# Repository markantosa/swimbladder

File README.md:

# SwimBladder

Power distribution board (PDB) project files for the SwimBladder project.

Silkscreen tag: `SOAR UWU | 8 x T200 | V1.1`

> [!WARNING]
> This board is an unvalidated, untested work in progress (WIP).
> It has not completed electrical, thermal, or in-water system validation.
> Do not treat this design as production-ready hardware.

## Project Status

- Current state: WIP (design in progress)
- Revision: V1.1
- Validation status: not electrically validated
- Test status: not thermally validated, not full-load validated, not field-tested
- Use at your own risk until formal verification is completed

## Repository Contents

- `KiCad Project Files v1.1/` - **Canonical** KiCad project, PCB, schematic, and the
  `SwimBladder Custom Footprints` library. Open `KiCad Project Files v1.1/UWU PDB.kicad_pro`.
- `KiCad Project Files/` - Deprecated earlier project set, kept for history. Do not edit.
- `SwimBladder PDB.kicad_sch` (repo root) - Stale May snapshot, superseded by the schematic
  inside `KiCad Project Files v1.1/`. Do not use.
- `Screenshots/` - Board and schematic screenshots. `v1.1 *.png` are current; the unprefixed
  files are the earlier V1.0 captures.
- `SwimBladderV1.0.step` - 3D board model (V1.0 geometry).
- `Swim_Bladder_Doc_v3_0.pdf` - Full engineering reference and calculations. Component values
  in this PDF predate the V1.1 schematic changes listed below.

## Project Overview

This board is designed as a compact 8-thruster central star-node PDB for Blue Robotics T200
systems with 4S battery input. It is currently in a pre-validation state and should be treated
as a reference design draft.

- System topology: battery -> cable-side main fuse -> optional e-stop/contactor -> dual XT90 input -> central high-current node -> 8 fused ESC branches -> XT60 outputs
- Nominal battery voltage: 14.8 V (4S), full charge: 16.8 V
- Thruster design current: about 25 A each
- Total design current: 200 A (with burst targets up to around 280-300 A)
- Per-branch fuse target: 30 A

## Schematic Summary (V1.1)

### Input / central node
- Dual XT90 input connectors (`J1`, `J19`) feeding one common +VBAT star node, symmetrical wiring for current sharing.
- Bulk capacitance at the node: `C_MAIN1`, `C_MAIN2` = 4700 uF each.
- Input TVS: `D1` (`D_TVS`), 22-24 V standoff class for 4S. Recommended part: SMDJ22A
  (unidirectional, 3 kW, DO-214AB / SMC footprint, `Diode_SMD:D_SMC` or `D_SMC_HandSolder`).
- Rail bleed / discharge: `R_BLEED1` = 22 kOhm. Draws ~0.76 mA / ~13 mW continuously at full
  charge - trivial dissipation for a 0603, well within its power/voltage rating.
- Power/status LED: `D2` (`LED`) with series resistor `R_LED1` = 10 kOhm.

### Per-ESC branch (x8)
- Branch fuse: `F_ESC1..F_ESC8` = 30 A.
- Branch bulk cap: `C_ESC1..C_ESC8` = 1000 uF.
- Branch high-frequency cap: `C_HF1..C_HF8` = 1 uF.
- Output: `J3..J10`, XT60 per branch.
- Branch decoupling is now two caps (1000 uF + 1 uF). The earlier third per-branch cap
  (1 nF high-frequency) has been removed - on a high-current motor branch it contributes
  negligible benefit and can create anti-resonance with the larger caps.

### PWM signal
- 16-pin IDC header `J2` (`Conn_02x08_Odd_Even`, 2x8, 2.54 mm), alternating PWM / GND pins.
  Suggested part footprint: `Connector_IDC:IDC-Header_2x08_P2.54mm_Vertical`.
- Individual PWM channel inputs: `J11..J18` (PWM1..PWM8).
- Per-channel series resistor: `R_PWM1..R_PWM8` = 100 Ohm.
- Per-channel pulldown resistor: `R_PD1..R_PD8` = 10 kOhm.

## Passive Footprint Notes

- PWM channel series resistors (`R_PWM*`): 0402 hand-solder land pattern
  (`Resistor_SMD:R_0402_1005Metric_Pad0.72x0.64mm_HandSolder`) for IDC header pitch.
- All other signal passives (`R_BLEED1`, `R_LED1`, `R_PD*`) and branch HF caps: 0603
  hand-solder (`R_0603_1608Metric_Pad0.98x0.95mm_HandSolder` /
  `C_0603_1608Metric_Pad1.08x0.95mm_HandSolder`).
- Custom / project-specific footprints live in `KiCad Project Files v1.1/SwimBladder Custom Footprints`.

## Key Engineering Notes (from the PDF)

- Architecture: single compact central +VBAT node, not dual banks, for a roughly 90 mm x 90 mm board.
- Safety: main fuse should be upstream on the battery cable (recommended 225-250 A), close to the battery.
- Copper strategy: use a short, wide, via-stitched central polygon (L1 + L3 for +VBAT), and strong common ground return (L2 + L4).
- Copper thickness for the 200 A / 300 A rating: 1 oz (35 um) is not sufficient. Spec 2 oz
  (70 um) minimum on the outer layers, 3 oz preferred, and carry +VBAT and GND on two layers
  each in parallel (~4 oz-equivalent per net) with dense inter-layer via stitching. Treat the
  central node as a plane, not a trace, and size pours/vias for <= 20-30 C rise. Per-branch
  (~25 A): 2 oz outer with ~10-15 mm pour width is adequate.
- Via stitching: use two via classes - large power vias (~1.2 mm pad / 0.6 mm drill or bigger)
  for the +VBAT node and ground return, and a smaller class (~0.6-0.8 mm pad / 0.3-0.4 mm drill)
  for signal-ground / thermal stitching around the PWM header.
- Branch geometry: practical branch widths around 12-15 mm (8-10 mm absolute compact minimum for very short sections).
- Connectors: dual XT90 input for current sharing (symmetrical wiring), XT60 per ESC branch preferred.
- Protection/passives: 22-24 V standoff TVS class for 4S input, bulk capacitance near input/node plus branch-level capacitors.
- Signal: 16-pin IDC PWM header with alternating PWM/GND and per-channel series + pulldown resistors.

## Known Issues / TODO (V1.1)

- No outstanding items. TVS placement, input HF cap grouping, indicator LEDs, and the
  `R_BLEED1` value (now 22 kOhm) have all been resolved.

## Quick Calculation Snapshot

- Per thruster power at 16 V and 25 A: 400 W
- System power for 8 thrusters: 3200 W
- Example central copper section in the doc (50 mm width, 140 um thickness, 25 mm length, one layer):
	- Estimated R ~= 0.0616 mOhm
	- Vdrop at 200 A ~= 0.012 V
	- Copper loss at 200 A ~= 2.46 W

For complete assumptions, formulas, BOM guidance, and test plan, see `Swim_Bladder_Doc_v3_0.pdf`.

## Screenshots (V1.1)

| Assembled Board (1) | Assembled Board (2) |
|---|---|
|  |  |

| Routing | 3D Render - Top | 3D Render - Isometric |
|---|---|---|
|  |  |  |

<sub>Earlier V1.0 captures (`Schematic.png`, `PCB Editor View.png`, `3D View.png`) remain in `Screenshots/` for reference.</sub>

## Getting Started

1. Install KiCad (recommended version 8+).
2. Open the project from `KiCad Project Files v1.1/UWU PDB.kicad_pro`.
3. Review schematic, layout, and engineering assumptions from the PDF before fabrication,
   noting the V1.1 changes and open TODO items above.

## Changelog

### V1.1 (in progress)
- Canonical project files moved to `KiCad Project Files v1.1/`; earlier `KiCad Project Files/`
  and the repo-root `SwimBladder PDB.kicad_sch` are deprecated.
- Added `SwimBladder Custom Footprints` library.
- Main bulk capacitance specified as `C_MAIN1/2` = 4700 uF each.
- Removed the 1 nF per-branch decoupling cap; branches now use 1000 uF + 1 uF only.
- PWM front-end defined: `R_PWM*` = 100 Ohm series, `R_PD*` = 10 kOhm pulldown, inputs `J11..J18`.
- Added rail bleed resistor `R_BLEED1` (value still a placeholder) and status LED `D2` / `R_LED1`.
- Input TVS `D1` present; placement correction pending (see Known Issues).

### V1.0
- Initial 8-branch central star-node PDB layout.

## Procurement (2-board build)

Bare PCB via JLCPCB; most components via LCSC (`SwimBladder_LCSC_BatchBOM_v1.1.csv`); full
reference BOM in `SwimBladder_BOM_v1.1.csv`. JLCPCB and LCSC ship separately even though they're
sister companies - no combined-box option outside of paying for JLC's PCBA assembly service.

### Still need to source separately (not in the LCSC batch order)
- [ ] `R_BLEED1`, 22k Ohm, 0603 (LCSC C114065) - MOQ is Min:100/Mult:100, not worth it for ~3
  pieces; ask around for spares or buy loose.
- [ ] `R_LED1` + `R_PD1..R_PD8`, 10k Ohm, 0603 (LCSC C98220) - same MOQ issue, ~23 pieces needed.
- [ ] 30 A mini blade fuse elements (x16) for `F_ESC1..F_ESC8` - these plug into the Keystone 3568
  holder (which is in the LCSC order) but the fuse element itself isn't an LCSC/electronics-
  distributor item; source from an automotive parts store or RC supplier.
- [ ] `F_ESC1..F_ESC8` fuseholders, Keystone 3568 (x8) - LCSC C5249699 was out of stock, dropped
  from the batch order; source from Digi-Key/Mouser instead.

### Already owned, not in the order
- `D2` status LED
- `J2` IDC 2x08 header
- `R_PWM1..R_PWM8`, 100 Ohm, 0402 (from sample book)

## License

This project is licensed under the MIT License. See the LICENSE file for details.

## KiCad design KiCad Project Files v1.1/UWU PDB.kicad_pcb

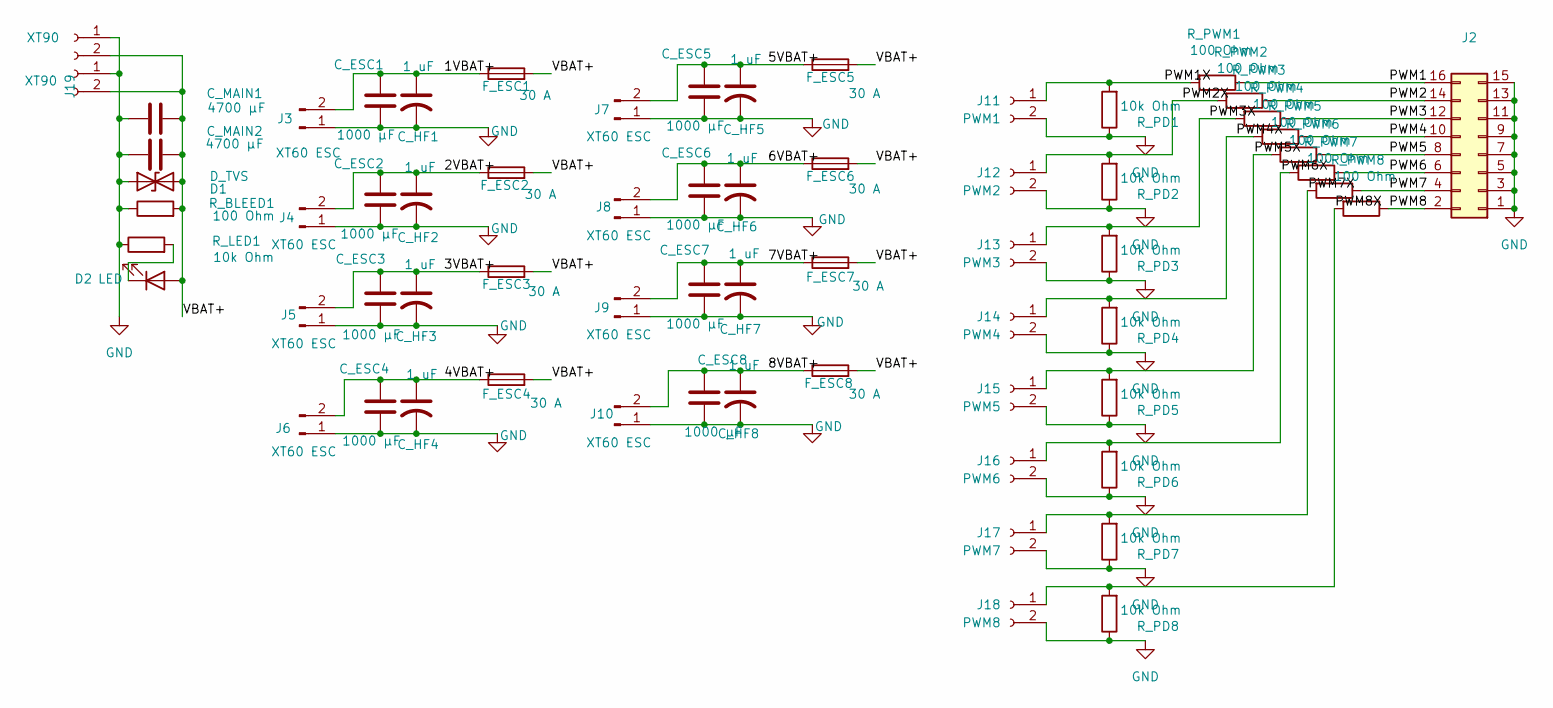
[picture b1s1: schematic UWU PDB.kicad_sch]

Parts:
C_ESC1, C_ESC2, C_ESC3, C_ESC4, C_ESC5, C_ESC6, C_ESC7, C_ESC8: 1000 µF; CP_Radial_D12.5mm_P5.00mm
C_HF1, C_HF2, C_HF3, C_HF4, C_HF5, C_HF6, C_HF7, C_HF8: 1 uF; C_0603_1608Metric_Pad1.08x0.95mm_HandSolder
C_MAIN1, C_MAIN2: 4700 µF; CP_Radial_D16.0mm_P7.50mm
D1: D_TVS; D_SMC
D2: LED; LED_1206_3216Metric
F_ESC1, F_ESC2, F_ESC3, F_ESC4, F_ESC5, F_ESC6, F_ESC7, F_ESC8: 30 A; Fuseholder_Blade_Mini_Keystone_3568
J1, J19: XT90; AMASS_XT90PW-M_1x02_P10.90mm_Horizontal
J2: Conn_02x08_Odd_Even; IDC-Header_2x08_P2.54mm_Vertical
J3, J4, J5, J6, J7, J8, J9, J10: XT60 ESC; AMASS_XT60PW-F_1x02_P7.20mm_Horizontal
J11: PWM1; Molex_Micro-Fit_3.0_43650-0200_1x02_P3.00mm_Horizontal
J12: PWM2; Molex_Micro-Fit_3.0_43650-0200_1x02_P3.00mm_Horizontal
J13: PWM3; Molex_Micro-Fit_3.0_43650-0200_1x02_P3.00mm_Horizontal
J14: PWM4; Molex_Micro-Fit_3.0_43650-0200_1x02_P3.00mm_Horizontal
J15: PWM5; Molex_Micro-Fit_3.0_43650-0200_1x02_P3.00mm_Horizontal
J16: PWM6; Molex_Micro-Fit_3.0_43650-0200_1x02_P3.00mm_Horizontal
J17: PWM7; Molex_Micro-Fit_3.0_43650-0200_1x02_P3.00mm_Horizontal
J18: PWM8; Molex_Micro-Fit_3.0_43650-0200_1x02_P3.00mm_Horizontal
R_BLEED1: 100 Ohm; R_0603_1608Metric_Pad0.98x0.95mm_HandSolder
R_LED1: 10k Ohm; R_0603_1608Metric_Pad0.98x0.95mm_HandSolder
R_PD1, R_PD2, R_PD3, R_PD4, R_PD5, R_PD6, R_PD7, R_PD8: 10k Ohm; R_0402_1005Metric_Pad0.72x0.64mm_HandSolder
R_PWM1, R_PWM2, R_PWM3, R_PWM4, R_PWM5, R_PWM6, R_PWM7, R_PWM8: 100 Ohm; R_0402_1005Metric_Pad0.72x0.64mm_HandSolder

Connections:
/1VBAT+: C_ESC1.1, C_HF1.1, F_ESC1.1, J3.2
/2VBAT+: C_ESC2.1, C_HF2.1, F_ESC2.1, J4.2
/3VBAT+: C_ESC3.1, C_HF3.1, F_ESC3.1, J5.2
/4VBAT+: C_ESC4.1, C_HF4.1, F_ESC4.1, J6.2
/5VBAT+: C_ESC5.1, C_HF5.1, F_ESC5.1, J7.2
/6VBAT+: C_ESC6.1, C_HF6.1, F_ESC6.1, J8.2
/7VBAT+: C_ESC7.1, C_HF7.1, F_ESC7.1, J9.2
/8VBAT+: C_ESC8.1, C_HF8.1, F_ESC8.1, J10.2
/PWM1: J2.16, R_PWM1.1
/PWM1X: J11.1, R_PD1.2, R_PWM1.2
/PWM2: J2.14, R_PWM2.1
/PWM2X: J12.1, R_PD2.2, R_PWM2.2
/PWM3: J2.12, R_PWM3.1
/PWM3X: J13.1, R_PD3.2, R_PWM3.2
/PWM4: J2.10, R_PWM4.1
/PWM4X: J14.1, R_PD4.2, R_PWM4.2
/PWM5: J2.8, R_PWM5.1
/PWM5X: J15.1, R_PD5.2, R_PWM5.2
/PWM6: J2.6, R_PWM6.1
/PWM6X: J16.1, R_PD6.2, R_PWM6.2
/PWM7: J2.4, R_PWM7.1
/PWM7X: J17.1, R_PD7.2, R_PWM7.2
/PWM8: J2.2, R_PWM8.1
/PWM8X: J18.1, R_PD8.2, R_PWM8.2
/VBAT+: C_MAIN1.1, C_MAIN2.1, D1.2 (A2), D2.2 (A), F_ESC1.2, F_ESC2.2, F_ESC3.2, F_ESC4.2, F_ESC5.2, F_ESC6.2, F_ESC7.2, F_ESC8.2, J1.2, J19.2, R_BLEED1.2
GND: C_ESC1.2, C_ESC2.2, C_ESC3.2, C_ESC4.2, C_ESC5.2, C_ESC6.2, C_ESC7.2, C_ESC8.2, C_HF1.2, C_HF2.2, C_HF3.2, C_HF4.2, C_HF5.2, C_HF6.2, C_HF7.2, C_HF8.2, C_MAIN1.2, C_MAIN2.2, D1.1 (A1), J1.1, J2.1, J2.3, J2.5, J2.7, J2.9, J2.11, J2.13, J2.15, J3.1, J4.1, J5.1, J6.1, J7.1, J8.1, J9.1, J10.1, J11.2, J12.2, J13.2, J14.2, J15.2, J16.2, J17.2, J18.2, J19.1, R_BLEED1.1, R_LED1.1, R_PD1.1, R_PD2.1, R_PD3.1, R_PD4.1, R_PD5.1, R_PD6.1, R_PD7.1, R_PD8.1
unnamed: D2.1 (K), R_LED1.2

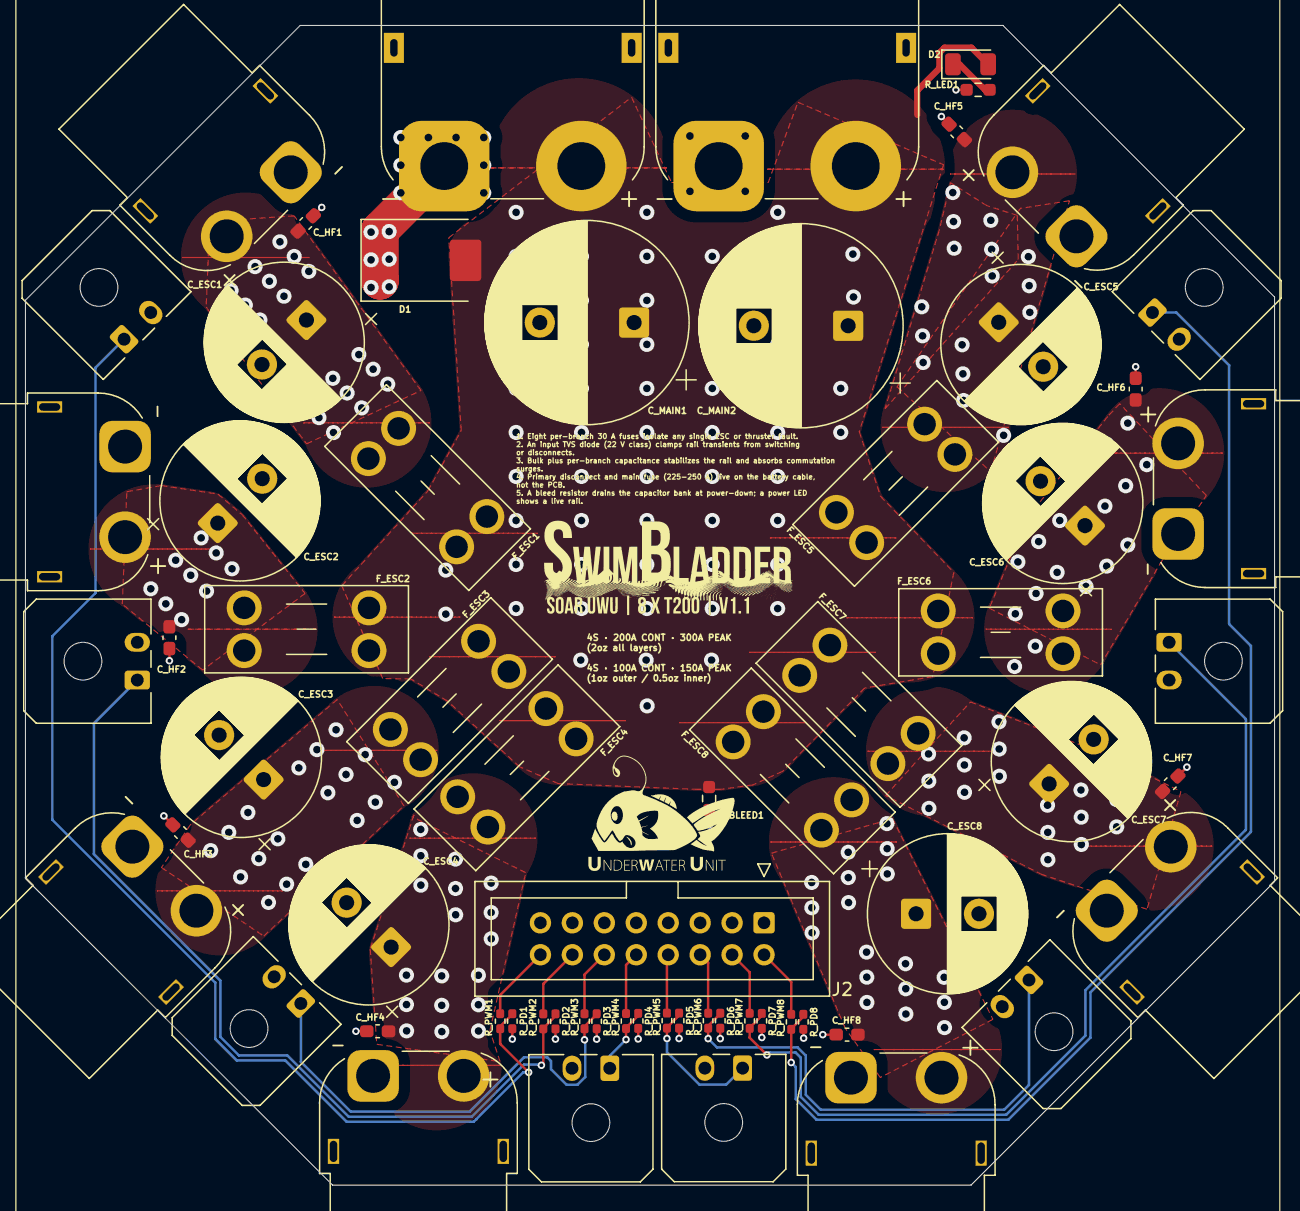
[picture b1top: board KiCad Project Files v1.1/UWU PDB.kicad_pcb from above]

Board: 4 copper layers, 99.3 x 92.2 mm, 65 parts (0 on the bottom side), 27 nets.

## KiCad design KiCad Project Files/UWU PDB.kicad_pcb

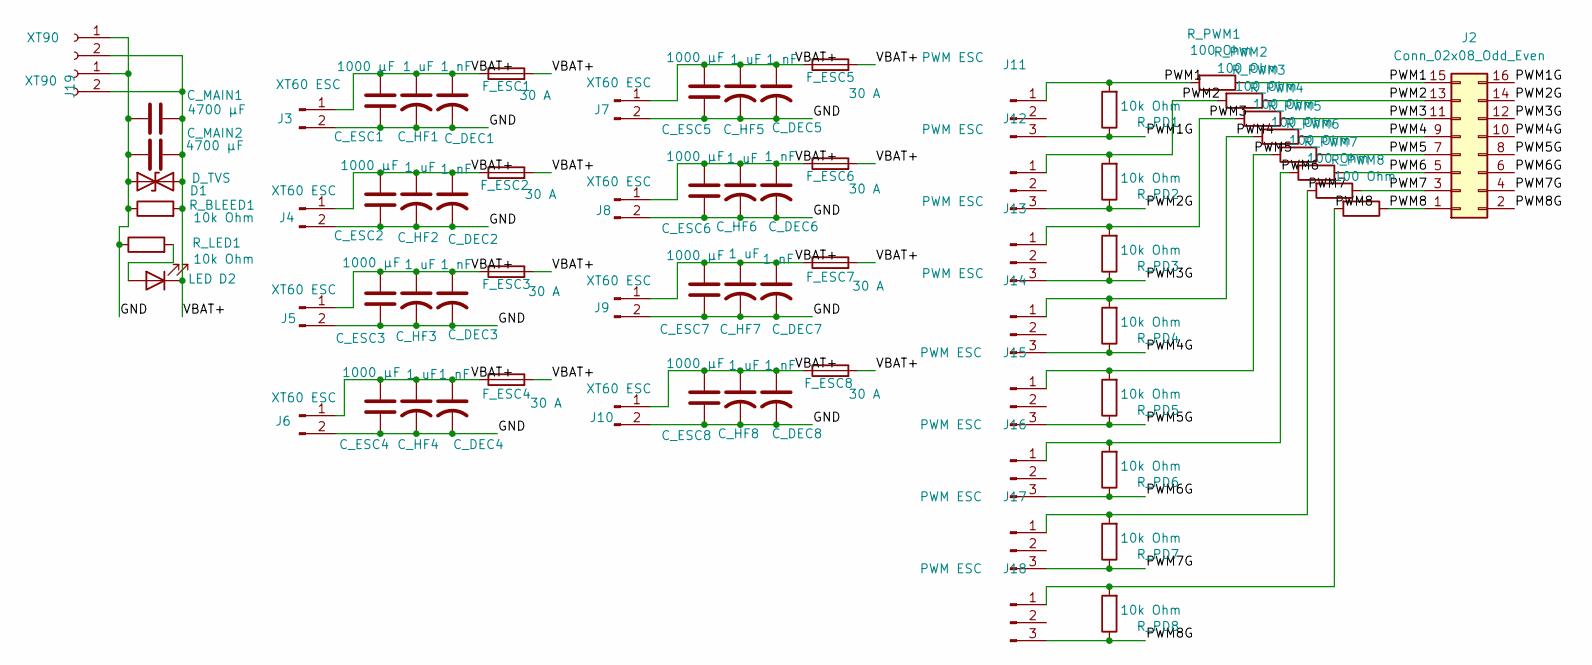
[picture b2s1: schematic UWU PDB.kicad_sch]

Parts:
C_DEC1, C_DEC2, C_DEC3, C_DEC4, C_DEC5, C_DEC6, C_DEC7, C_DEC8: 1 nF; C_1206_3216Metric_Pad1.33x1.80mm_HandSolder
C_ESC1, C_ESC2, C_ESC3, C_ESC4, C_ESC5, C_ESC6, C_ESC7, C_ESC8: 1000 µF; CP_Radial_D12.5mm_P5.00mm
C_HF1, C_HF2, C_HF3, C_HF4, C_HF5, C_HF6, C_HF7, C_HF8: 1 uF; C_1206_3216Metric_Pad1.33x1.80mm_HandSolder
C_MAIN1, C_MAIN2: 4700 µF; CP_Radial_D16.0mm_P7.50mm
D1: D_TVS; D_SMC
D2: LED; LED_1206_3216Metric
F_ESC1, F_ESC2, F_ESC3, F_ESC4, F_ESC5, F_ESC6, F_ESC7, F_ESC8: 30 A; Fuseholder_Blade_Mini_Keystone_3568
J1, J19: XT90; AMASS_XT90PW-M_1x02_P10.90mm_Horizontal
J2: Conn_02x08_Odd_Even; PinSocket_2x08_P2.00mm_Vertical
J3, J4, J5, J6, J7, J8, J9, J10: XT60 ESC; AMASS_XT60PW-F_1x02_P7.20mm_Horizontal
J11, J12, J13, J14, J15, J16, J17, J18: PWM ESC; PinHeader_1x03_P2.54mm_Horizontal
R_BLEED1: 10k Ohm; R_1206_3216Metric
R_LED1: 10k Ohm; R_1206_3216Metric
R_PD1, R_PD2, R_PD3, R_PD4, R_PD5, R_PD6, R_PD7, R_PD8: 10k Ohm; R_1206_3216Metric
R_PWM1, R_PWM2, R_PWM3, R_PWM4, R_PWM5, R_PWM6, R_PWM7, R_PWM8: 100 Ohm; R_1206_3216Metric

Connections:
/GND: C_DEC1.2, C_DEC2.2, C_DEC3.2, C_DEC4.2, C_DEC5.2, C_DEC6.2, C_DEC7.2, C_DEC8.2, C_ESC1.1, C_ESC2.1, C_ESC3.1, C_ESC4.1, C_ESC5.1, C_ESC6.1, C_ESC7.1, C_ESC8.1, C_HF1.2, C_HF2.2, C_HF3.2, C_HF4.2, C_HF5.2, C_HF6.2, C_HF7.2, C_HF8.2, C_MAIN1.2, C_MAIN2.2, D1.1 (A1), J1.1, J3.2, J4.2, J5.2, J6.2, J7.2, J8.2, J9.2, J10.2, J19.1, R_BLEED1.1, R_LED1.1
/PWM1: J2.15, J11.1, R_PD1.2, R_PWM1.1, R_PWM1.2
/PWM1G: J2.16, J11.3, R_PD1.1
/PWM2: J2.13, J12.1, R_PD2.2, R_PWM2.1, R_PWM2.2
/PWM2G: J2.14, J12.3, R_PD2.1
/PWM3: J2.11, J13.1, R_PD3.2, R_PWM3.1, R_PWM3.2
/PWM3G: J2.12, J13.3, R_PD3.1
/PWM4: J2.9, J14.1, R_PD4.2, R_PWM4.1, R_PWM4.2
/PWM4G: J2.10, J14.3, R_PD4.1
/PWM5: J2.7, J15.1, R_PD5.2, R_PWM5.1, R_PWM5.2
/PWM5G: J2.8, J15.3, R_PD5.1
/PWM6: J2.5, J16.1, R_PD6.2, R_PWM6.1, R_PWM6.2
/PWM6G: J2.6, J16.3, R_PD6.1
/PWM7: J2.3, J17.1, R_PD7.2, R_PWM7.1, R_PWM7.2
/PWM7G: J2.4, J17.3, R_PD7.1
/PWM8: J2.1, J18.1, R_PD8.2, R_PWM8.1, R_PWM8.2
/PWM8G: J2.2, J18.3, R_PD8.1
/VBAT+: C_DEC1.1, C_DEC2.1, C_DEC3.1, C_DEC4.1, C_DEC5.1, C_DEC6.1, C_DEC7.1, C_DEC8.1, C_ESC1.2, C_ESC2.2, C_ESC3.2, C_ESC4.2, C_ESC5.2, C_ESC6.2, C_ESC7.2, C_ESC8.2, C_HF1.1, C_HF2.1, C_HF3.1, C_HF4.1, C_HF5.1, C_HF6.1, C_HF7.1, C_HF8.1, C_MAIN1.1, C_MAIN2.1, D1.2 (A2), D2.1 (K), F_ESC1.1, F_ESC1.2, F_ESC2.1, F_ESC2.2, F_ESC3.1, F_ESC3.2, F_ESC4.1, F_ESC4.2, F_ESC5.1, F_ESC5.2, F_ESC6.1, F_ESC6.2, F_ESC7.1, F_ESC7.2, F_ESC8.1, F_ESC8.2, J1.2, J3.1, J4.1, J5.1, J6.1, J7.1, J8.1, J9.1, J10.1, J19.2, R_BLEED1.2
unnamed: D2.2 (A), R_LED1.2

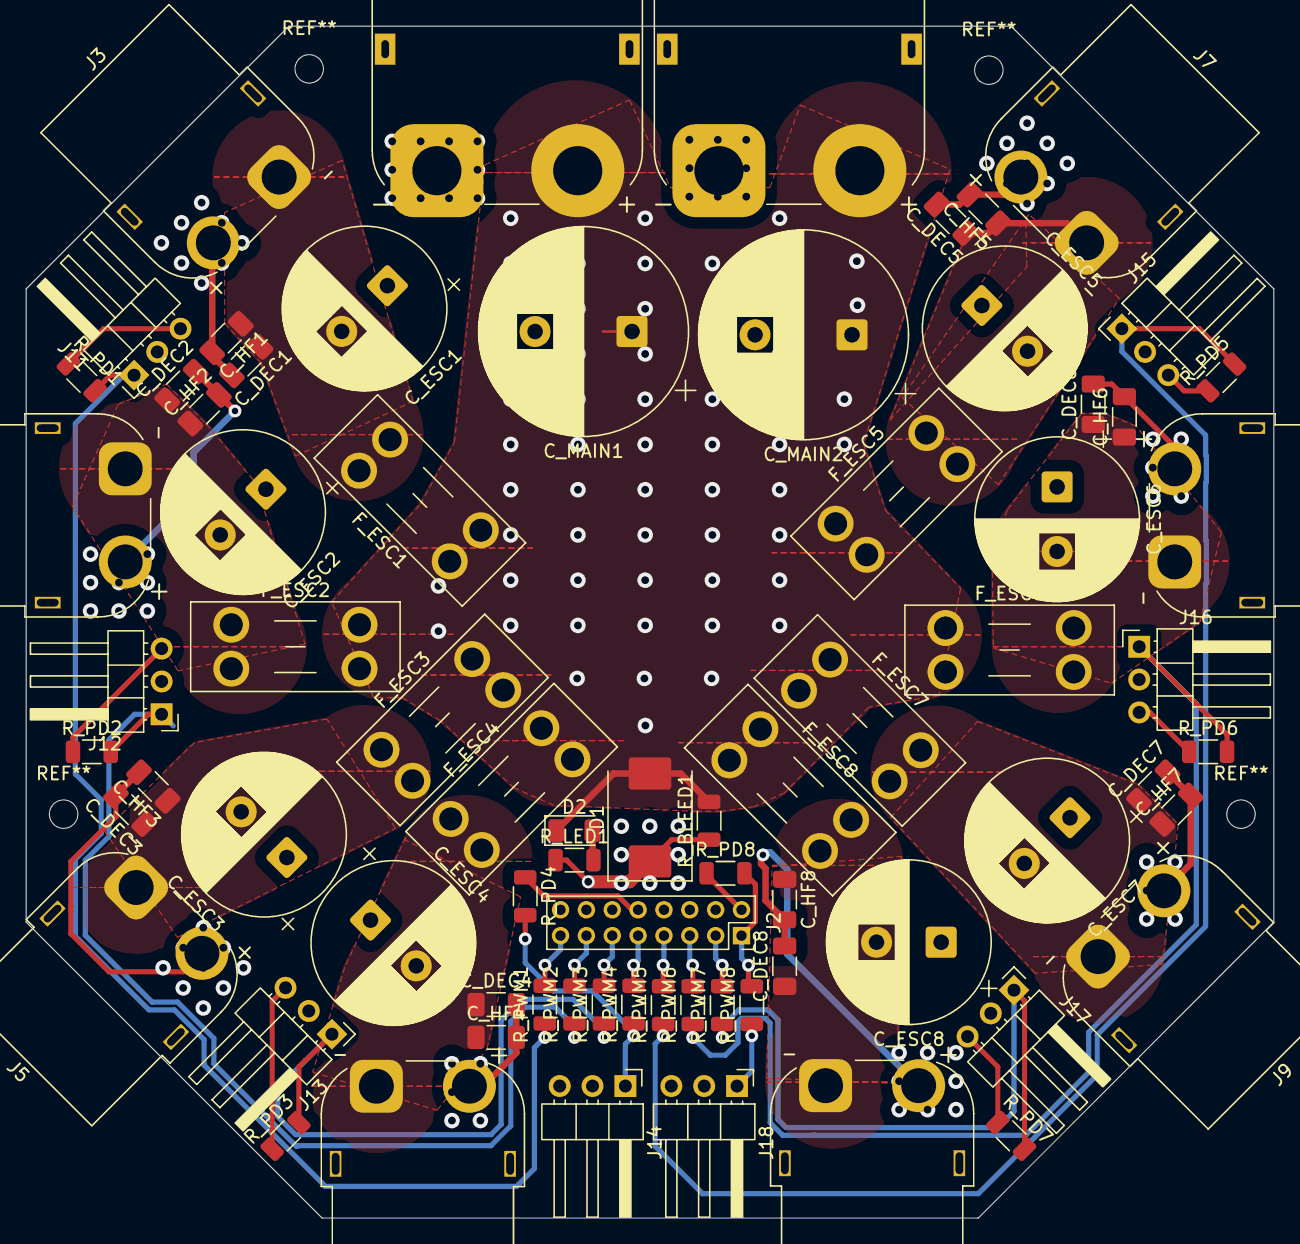
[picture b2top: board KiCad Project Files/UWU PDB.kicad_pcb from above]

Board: 4 copper layers, 96.5 x 92.2 mm, 73 parts (0 on the bottom side), 19 nets.

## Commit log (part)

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2026-05-27 Initial commit: add README, LICENSE, and KiCad project files
2026-05-27 Remove nested .history repos and ignore workspace metadata
2026-05-27 Enhance README with PDF-based engineering summary and scaled screenshots
2026-05-27 Add SwimBladder V1.0 STEP model
2026-05-27 Clarify README with prominent WIP and untested status
2026-05-27 Update KiCad design files and refresh screenshots
